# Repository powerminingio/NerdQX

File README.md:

<sup>Revision 1.0</sup>

> The standard and spearhead of current multi-ASIC home miners based on open hardware.

## About

**Powermining fork** changes are - removed USA flag, added Powermining logo

**NerdQX** is a new development based on [NerdQaxe++](https://github.com/shufps/qaxe). NerdQX also has four BM1370 ASIC
chips, a different PCB geometry, and significantly improved and simplified safety mechanisms. 

The NerdQX was developed as the world's first multi-ASIC home miner for overclocking, which also enables extremely 
efficient mining. Furthermore, the NerdQX can measure the temperature of all four ASICs separately and directly, in 
addition to the existing and somewhat less accurate variant. 

NerdQX offers full compatibility with the [ESP Miner NerdQAxe+](https://github.com/shufps/ESP-Miner-NerdQAxePlus) 
firmware, which has been specially enhanced for the NerdQX. This means you get the benefits of ongoing support and 
further development on an open source basis. 

Many small and large improvements make the NerdQX the new standard for multi-ASIC home miners based on open hardware.

## Highlights

### Four ASIC BM1370 processors with clock speeds up to 1000 MHz
> Unique in open-source home mining worldwide – ready for performance or economy mode.

### New PCB design with significantly increased copper and optimized conductor tracks
> The entire layout of the NerdQX has been redesigned electrically and thermally. The use of a significantly higher 
  copper ratio in the conductor tracks significantly improves the current carrying capacity of the board – even 
  under permanently high ASIC loads. The wider spacing and targeted routing ensure stable power supply, reduced heat 
  loss, and more even temperature distribution, while at the same time greatly improving efficiency.

### Dedicated cooling of the VREGs with custom-made heat sinks
> Unlike previous DIY miners, where voltage regulators often remain completely uncooled, NerdQX sets a new standard 
  here: The VREGs have been mechanically offset to enable the best possible airflow and heat dissipation. 
  In combination with a customized, thermally adapted heat sink, the resulting power loss is efficiently dissipated – 
  a concept that has previously only been used in industrial mining rigs. This measure not only extends the service 
  life of the components, but also allows safe overclocking without the risk of thermal instability in the power range 
  for the first time.
  
> **NOTE:** This heatsink is available from [Ix Tech](https://ixtech.xyz) not DigiKey.

### XT60 power connector
> Industry standard: extremely low contact resistance, high current carrying capacity, and reliable contact - even 
  in mobile or vibration-prone setups.

### Mini automotive fuse, set to the NerdQX power rating of 15 amps
> Robust, cost-effective, and easy to replace – provides additional protection against short circuits or overcurrent 
  without the need for complicated safety mechanisms, while allowing for simple visual checks of functionality.

### 4-pin PWM connector for up to three fans or AiO cooling
> Modular, efficient, prepared for quiet or aggressive cooling strategies.

### Rounded PCB corners for better protection and a high-quality overall impression
> A detail that makes safety and manufacturing quality visible.

### Proprietary open-source firmware
> The NerdQX firmware is based on the established open source NerdQaxe++ firmware, but has been specifically 
  enhanced for the new design and architecture of the NerdQX. These adjustments allow the NerdQX to be precisely 
  controlled in the range from underclocking to high-performance operation without compromising security or 
  transparency.

### Significantly improved sensor technology for temperature monitoring of all four ASICs
> Precise temperature measurement allows perfect control over thermal development during cooling. In addition to the 
  not entirely accurate temperature measurement of the ASIC, the NerdQX allows direct measurement and output of the 
  current temperature per ASIC processor for the first time.

## Collaboration

The NerdQX project was developed by an international team of enthusiasts. 

| Ix Tech                                                      | PlebBase                                                         | phil31                                                          | shufps                                                           |
|--------------------------------------------------------------|------------------------------------------------------------------|------------------------------------------------------------------|------------------------------------------------------------------|
|   |  |  |  |
|  |        |                                                                  |                                                                 |
 
> Special thanks go to shufps, who developed the NerdQaxe and the corresponding firmware; without him, much of this would
  not have been possible. Thanks also go to the many other talented developers who have been involved in the Nerd* 
  projects so far.

## Development

The further development of the NerdQX is being actively pursued in order to develop additional ideas and features with
the goal of creating the perfect multi-ASIC home miner that sets new standards.

## Table of Content

* [NerdQX original sources](assets/ORIGINAL_SOURCES.md)
* [NerdQX review on PlebBase](https://plebbase.com/development/all-eyez-nerdqx)
* [Official firmware](https://github.com/shufps/ESP-Miner-NerdQAxePlus)
* [Changelog](assets/CHANGELOG.md) of the project.

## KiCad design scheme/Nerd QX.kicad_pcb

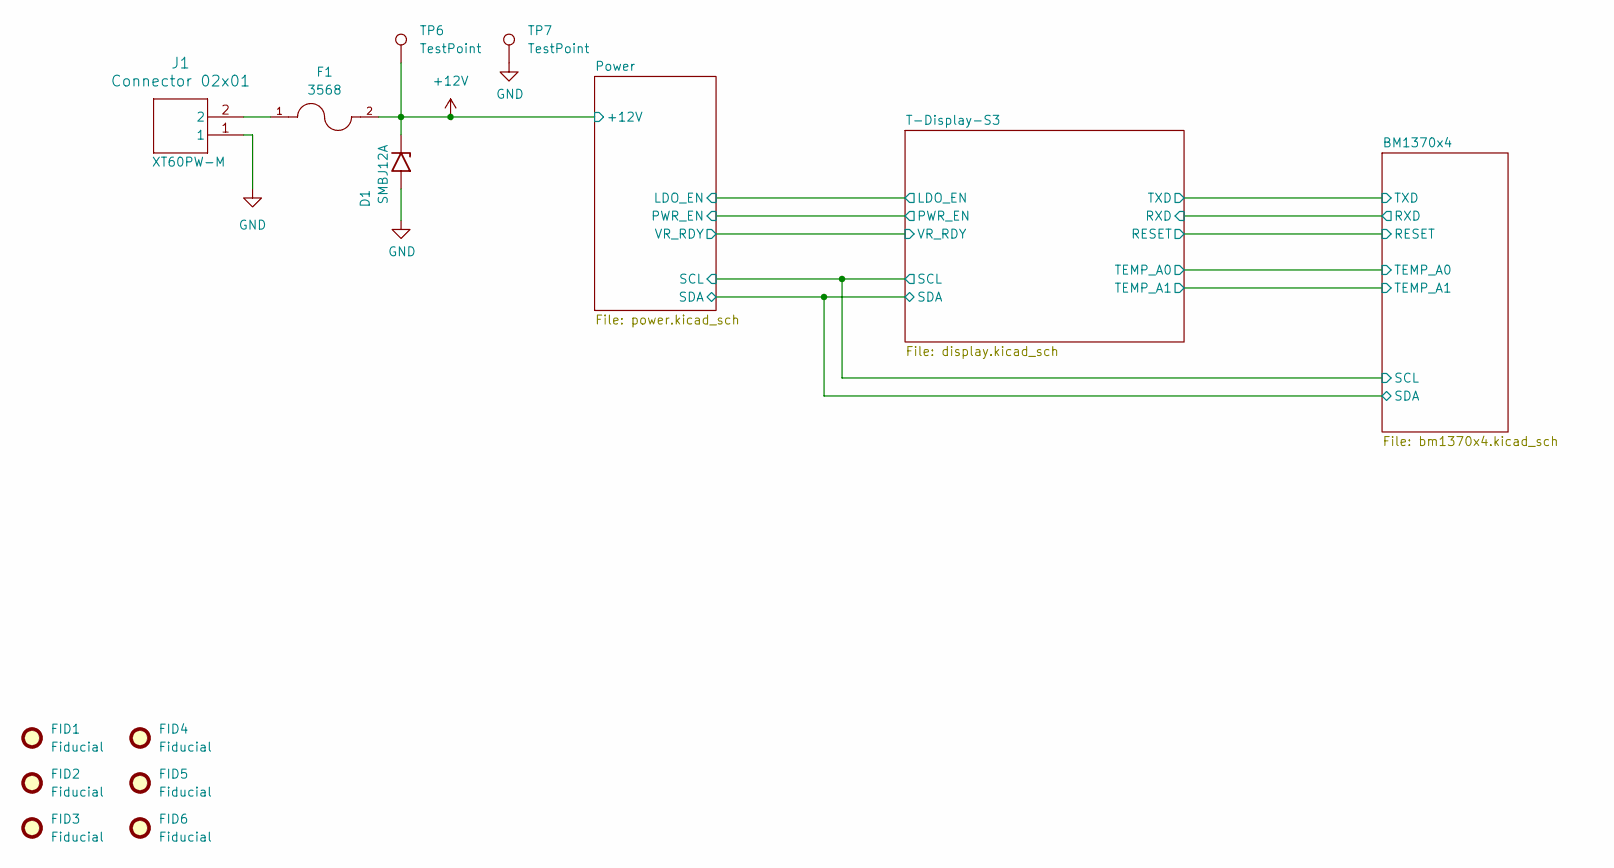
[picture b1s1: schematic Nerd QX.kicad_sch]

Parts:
D1: SMBJ12A; D_SMB
F1: 3568; Fuseholder_Blade_Mini_Keystone_3568
FID1, FID2, FID3, FID4, FID5, FID6: Fiducial; Fiducial_1mm_Mask3mm
J1: Connector 02x01; AMASS_XT60PW-M_1x02_P7.20mm_Horizontal
TP6, TP7: TestPoint; TestPoint_Pad_D2.0mm

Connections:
+12V: D1.1 (A1), F1.2, TP6.1; also elsewhere on the board
GND: D1.2 (A2), J1.1, TP7.1; also elsewhere on the board
unnamed: F1.1, J1.2

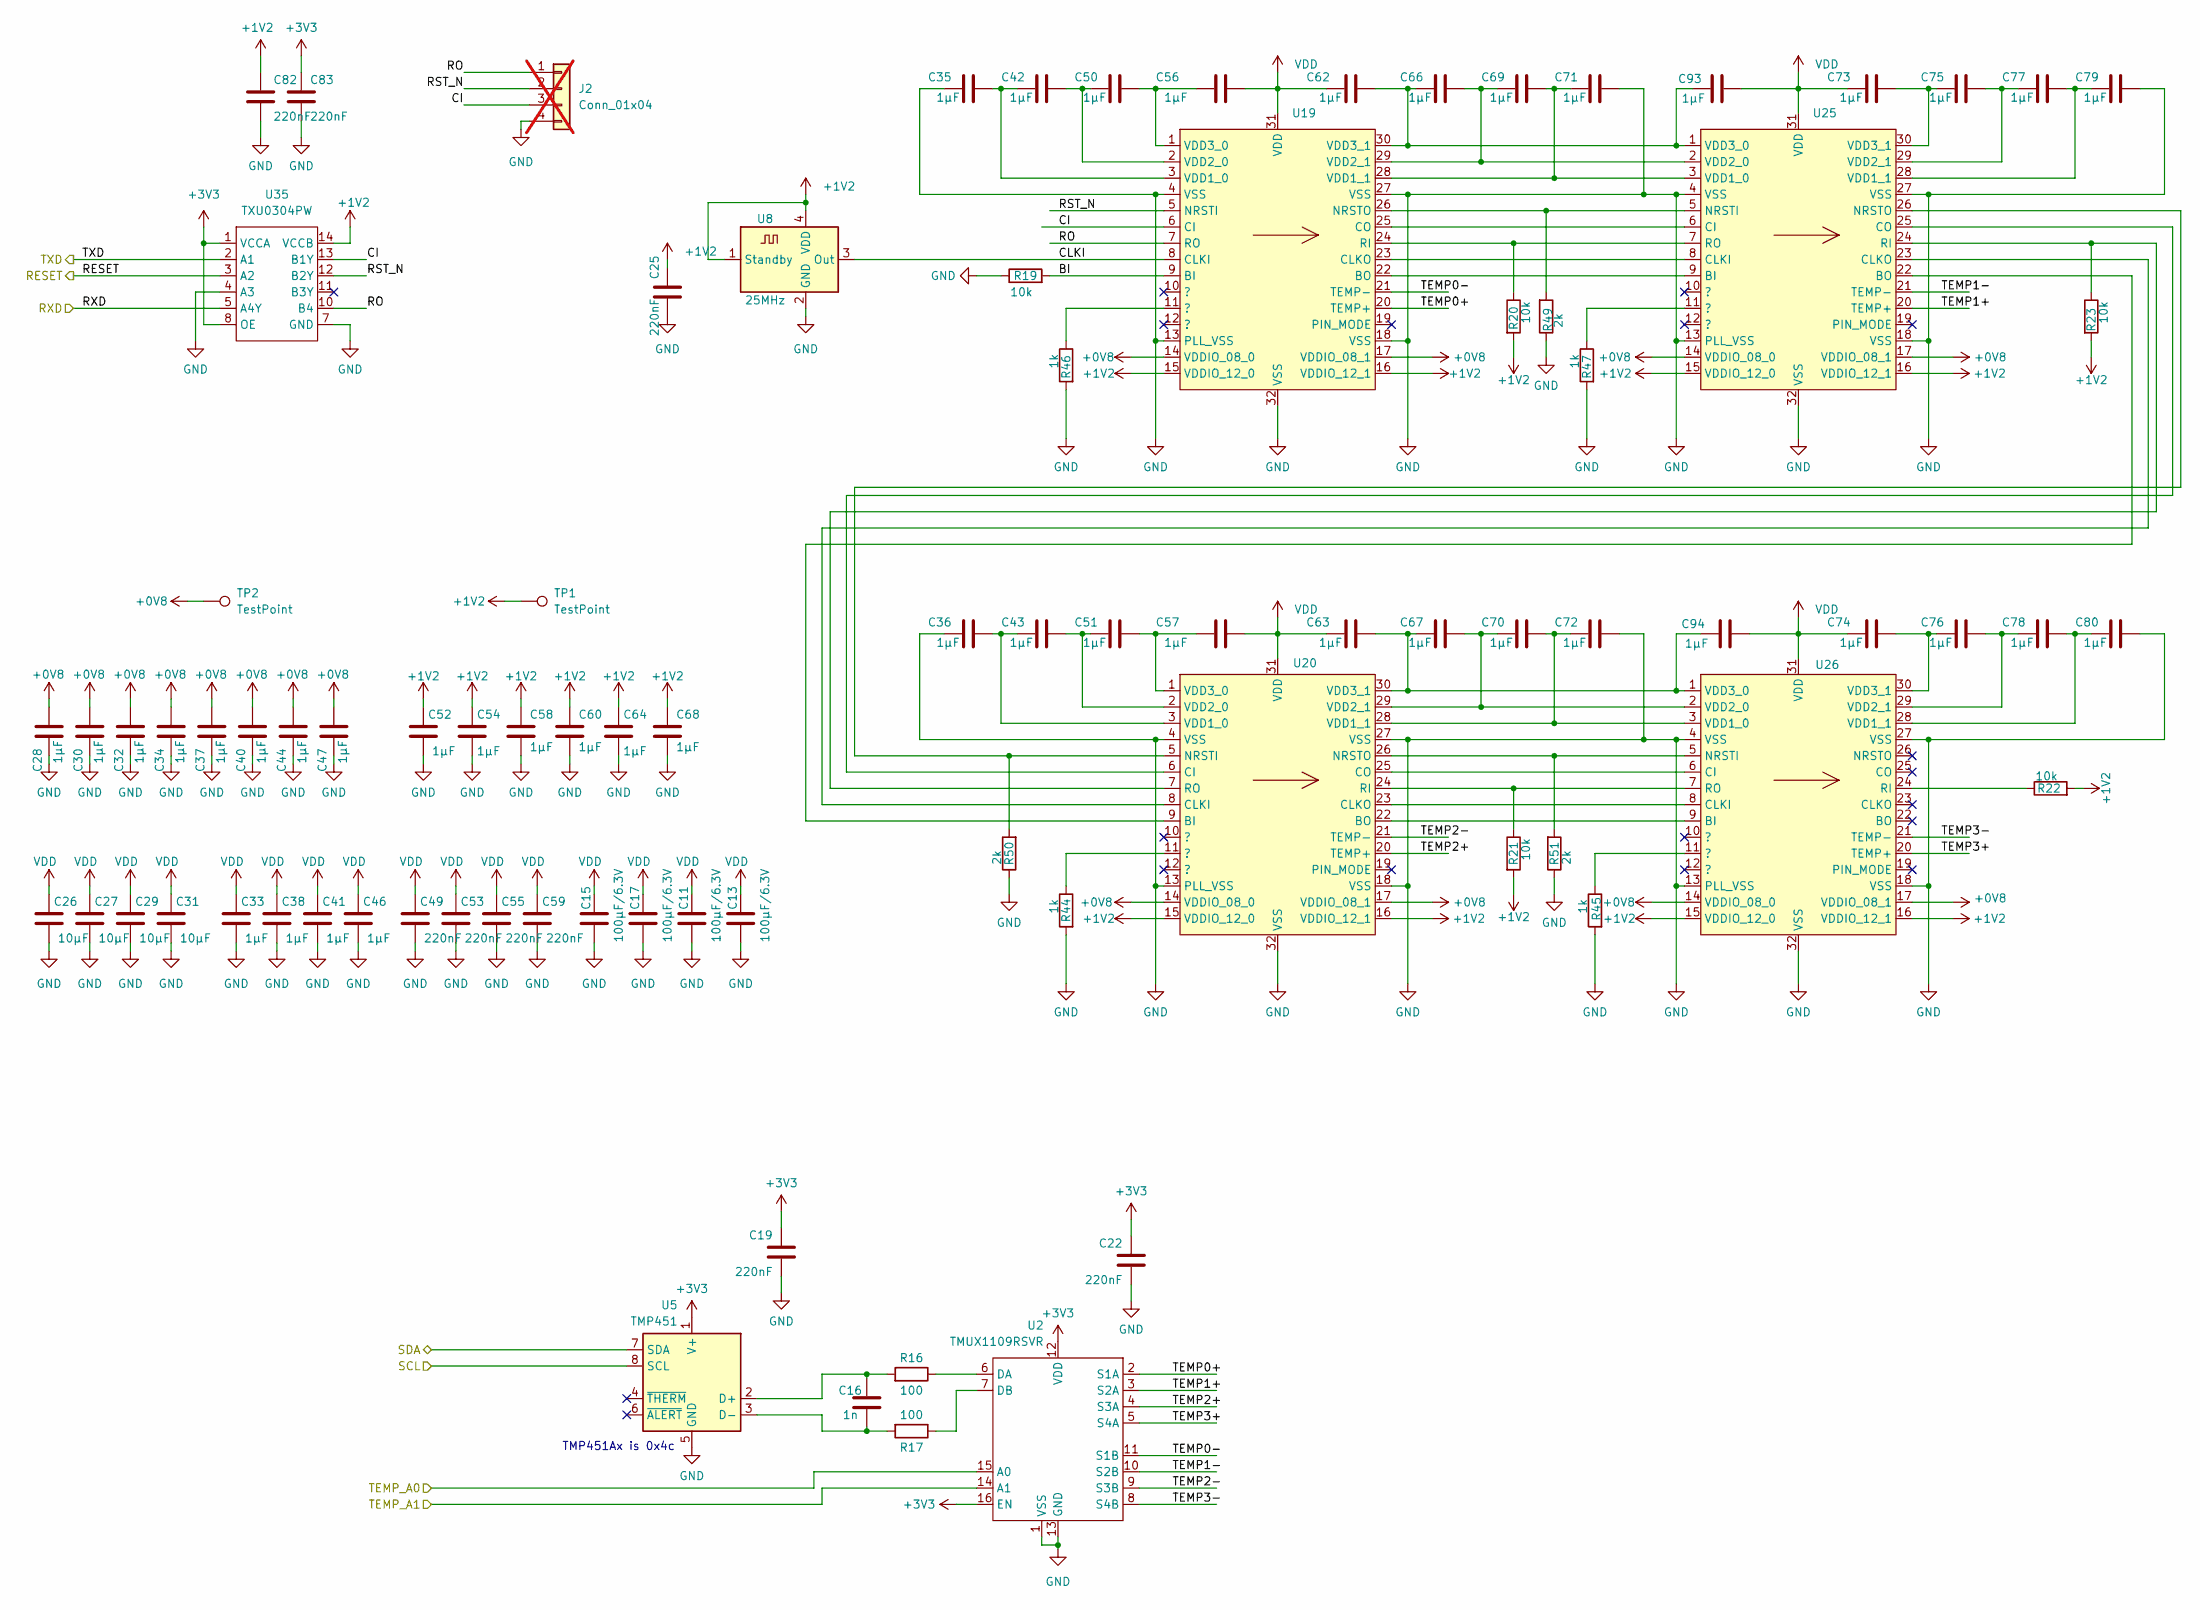
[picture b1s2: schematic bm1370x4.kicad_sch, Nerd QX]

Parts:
C11, C13, C15, C17: 100µF/6.3V; C_1210_3225Metric
C16: 1n; C_0805_2012Metric
C19, C22, C25, C49, C53, C55, C59, C82, C83: 220nF; C_0805_2012Metric
C26, C27, C29, C31: 10µF; C_0805_2012Metric
C28, C30, C32, C33, C34, C35, C36, C37, C38, C40, C41, C42, C43, C44, C46, C47, C50, C51, C52, C54, C56, C57, C58, C60, C62, C63, C64, C66, C67, C68, C69, C70, C71, C72, C73, C74, C75, C76, C77, C78, C79, C80, C93, C94: 1µF; C_0805_2012Metric
J2: Conn_01x04; PinHeader_1x04_P1.27mm_Vertical; not fitted
R16, R17: 100; R_0805_2012Metric
R19, R20, R21, R22, R23: 10k; R_0805_2012Metric
R44, R45, R46, R47: 1k; R_0805_2012Metric
R49, R50, R51: 2k; R_0805_2012Metric
TP1, TP2: TestPoint; TestPoint_Pad_D2.0mm
U2: TMUX1109RSVR; UQFN-16_1.8x2.6mm_P0.4mm
U5: TMP451; WSON-8-1EP_2x2mm_P0.5mm_EP0.9x1.6mm
U8: 25MHz; Oscillator_SMD_EuroQuartz_XO32-4Pin_3.2x2.5mm
U19, U20, U25, U26: BM1370_mode1; BM1370
U35: TXU0304PW; TSSOP-14_4.4x5mm_P0.65mm

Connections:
+0V8: C28.2, C30.2, C32.2, C34.2, C37.2, C40.2, C44.2, C47.2, TP2.1, U19.14 (VDDIO_08_0), U19.17 (VDDIO_08_1), U20.14 (VDDIO_08_0), U20.17 (VDDIO_08_1), U25.14 (VDDIO_08_0), U25.17 (VDDIO_08_1), U26.14 (VDDIO_08_0), U26.17 (VDDIO_08_1); also elsewhere on the board
+1V2: C25.1, C52.1, C54.1, C58.1, C60.1, C64.1, C68.1, C82.1, R20.2, R21.2, R22.2, R23.2, TP1.1, U8.1 (Standby), U8.4 (VDD), U19.15 (VDDIO_12_0), U19.16 (VDDIO_12_1), U20.15 (VDDIO_12_0), U20.16 (VDDIO_12_1), U25.15 (VDDIO_12_0), U25.16 (VDDIO_12_1), U26.15 (VDDIO_12_0), U26.16 (VDDIO_12_1), U35.14 (VCCB); also elsewhere on the board
+3V3: C19.1, C22.1, C83.1, U2.12 (VDD), U2.16 (EN), U5.1 (V+), U35.1 (VCCA), U35.8 (OE); also elsewhere on the board
/BM1370x4/BI: R19.2, U19.9 (BI)
/BM1370x4/CI: J2.3, U19.6 (CI), U35.13 (B1Y)
/BM1370x4/CLKI: U8.3 (Out), U19.8 (CLKI)
/BM1370x4/RESET: U35.3 (A2); also elsewhere on the board
/BM1370x4/RO: J2.1, U19.7 (RO), U35.10 (B4)
/BM1370x4/RST_N: J2.2, U19.5 (NRSTI), U35.12 (B2Y)
/BM1370x4/RXD: U35.5 (A4Y); also elsewhere on the board
/BM1370x4/TEMP0+: U2.2 (S1A), U19.20 (TEMP+)
/BM1370x4/TEMP0-: U2.11 (S1B), U19.21 (TEMP-)
/BM1370x4/TEMP1+: U2.3 (S2A), U25.20 (TEMP+)
/BM1370x4/TEMP1-: U2.10 (S2B), U25.21 (TEMP-)
/BM1370x4/TEMP2+: U2.4 (S3A), U20.20 (TEMP+)
/BM1370x4/TEMP2-: U2.9 (S3B), U20.21 (TEMP-)
/BM1370x4/TEMP3+: U2.5 (S4A), U26.20 (TEMP+)
/BM1370x4/TEMP3-: U2.8 (S4B), U26.21 (TEMP-)
/BM1370x4/TEMP_A0: U2.15 (A0); also elsewhere on the board
/BM1370x4/TEMP_A1: U2.14 (A1); also elsewhere on the board
/BM1370x4/TXD: U35.2 (A1); also elsewhere on the board
/T-Display-S3/SCL: U5.8 (SCL); also elsewhere on the board
/T-Display-S3/SDA: U5.7 (SDA); also elsewhere on the board
GND: C11.2, C13.2, C15.2, C17.2, C19.2, C22.2, C25.2, C26.2, C27.2, C28.1, C29.2, C30.1, C31.2, C32.1, C33.2, C34.1, C35.1, C36.1, C37.1, C38.2, C40.1, C41.2, C44.1, C46.2, C47.1, C49.2, C52.2, C53.2, C54.2, C55.2, C58.2, C59.2, C60.2, C64.2, C68.2, C71.2, C72.2, C79.2, C80.2, C82.2, C83.2, J2.4, R19.1, R44.2, R45.2, R46.2, R47.2, R49.1, R50.1, R51.1, U2.1 (VSS), U2.13 (GND), U5.5 (GND), U8.2 (GND), U19.4 (VSS), U19.13 (PLL_VSS), U19.18 (VSS), U19.27 (VSS), U19.32 (VSS), U20.4 (VSS), U20.13 (PLL_VSS), U20.18 (VSS), U20.27 (VSS), U20.32 (VSS), U25.4 (VSS), U25.13 (PLL_VSS), U25.18 (VSS), U25.27 (VSS), U25.32 (VSS), U26.4 (VSS), U26.13 (PLL_VSS), U26.18 (VSS), U26.27 (VSS), U26.32 (VSS), U35.4 (A3), U35.7 (GND); also elsewhere on the board
unnamed: R44.1, U20.11 (?)
unnamed: R45.1, U26.11 (?)
unnamed: R46.1, U19.11 (?)
unnamed: R47.1, U25.11 (?)
unnamed: R16.1, U2.6 (DA)
unnamed: R17.1, U2.7 (DB)
unnamed: C16.1, R16.2, U5.2 (D+)
unnamed: C16.2, R17.2, U5.3 (D-)
unnamed: U19.22 (BO), U25.9 (BI)
unnamed: U19.23 (CLKO), U25.8 (CLKI)
unnamed: U19.25 (CO), U25.6 (CI)
unnamed: R49.2, U19.26 (NRSTO), U25.5 (NRSTI)
unnamed: R20.1, U19.24 (RI), U25.7 (RO)
unnamed: C35.2, C42.1, U19.3 (VDD1_0)
unnamed: C69.2, C71.1, U19.28 (VDD1_1), U25.3 (VDD1_0)
unnamed: C42.2, C50.1, U19.2 (VDD2_0)
unnamed: C66.2, C69.1, U19.29 (VDD2_1), U25.2 (VDD2_0)
unnamed: C50.2, C56.1, U19.1 (VDD3_0)
unnamed: C62.2, C66.1, C93.1, U19.30 (VDD3_1), U25.1 (VDD3_0)
unnamed: U20.9 (BI), U25.22 (BO)
unnamed: U20.22 (BO), U26.9 (BI)
unnamed: U20.6 (CI), U25.25 (CO)
unnamed: U20.8 (CLKI), U25.23 (CLKO)
unnamed: U20.23 (CLKO), U26.8 (CLKI)
unnamed: U20.25 (CO), U26.6 (CI)
unnamed: R50.2, U20.5 (NRSTI), U25.26 (NRSTO)
unnamed: R51.2, U20.26 (NRSTO), U26.5 (NRSTI)
unnamed: R21.1, U20.24 (RI), U26.7 (RO)
unnamed: R23.1, U20.7 (RO), U25.24 (RI)
unnamed: C36.2, C43.1, U20.3 (VDD1_0)
unnamed: C70.2, C72.1, U20.28 (VDD1_1), U26.3 (VDD1_0)
unnamed: C43.2, C51.1, U20.2 (VDD2_0)
unnamed: C67.2, C70.1, U20.29 (VDD2_1), U26.2 (VDD2_0)
unnamed: C51.2, C57.1, U20.1 (VDD3_0)
unnamed: C63.2, C67.1, C94.1, U20.30 (VDD3_1), U26.1 (VDD3_0)
unnamed: C77.2, C79.1, U25.28 (VDD1_1)
unnamed: C75.2, C77.1, U25.29 (VDD2_1)
unnamed: C73.2, C75.1, U25.30 (VDD3_1)
unnamed: R22.1, U26.24 (RI)
unnamed: C78.2, C80.1, U26.28 (VDD1_1)
unnamed: C76.2, C78.1, U26.29 (VDD2_1)
unnamed: C74.2, C76.1, U26.30 (VDD3_1)
VDD: C11.1, C13.1, C15.1, C17.1, C26.1, C27.1, C29.1, C31.1, C33.1, C38.1, C41.1, C46.1, C49.1, C53.1, C55.1, C56.2, C57.2, C59.1, C62.1, C63.1, C73.1, C74.1, C93.2, C94.2, U19.31 (VDD), U20.31 (VDD), U25.31 (VDD), U26.31 (VDD); also elsewhere on the board

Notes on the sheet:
TMP451Ax is 0x4c

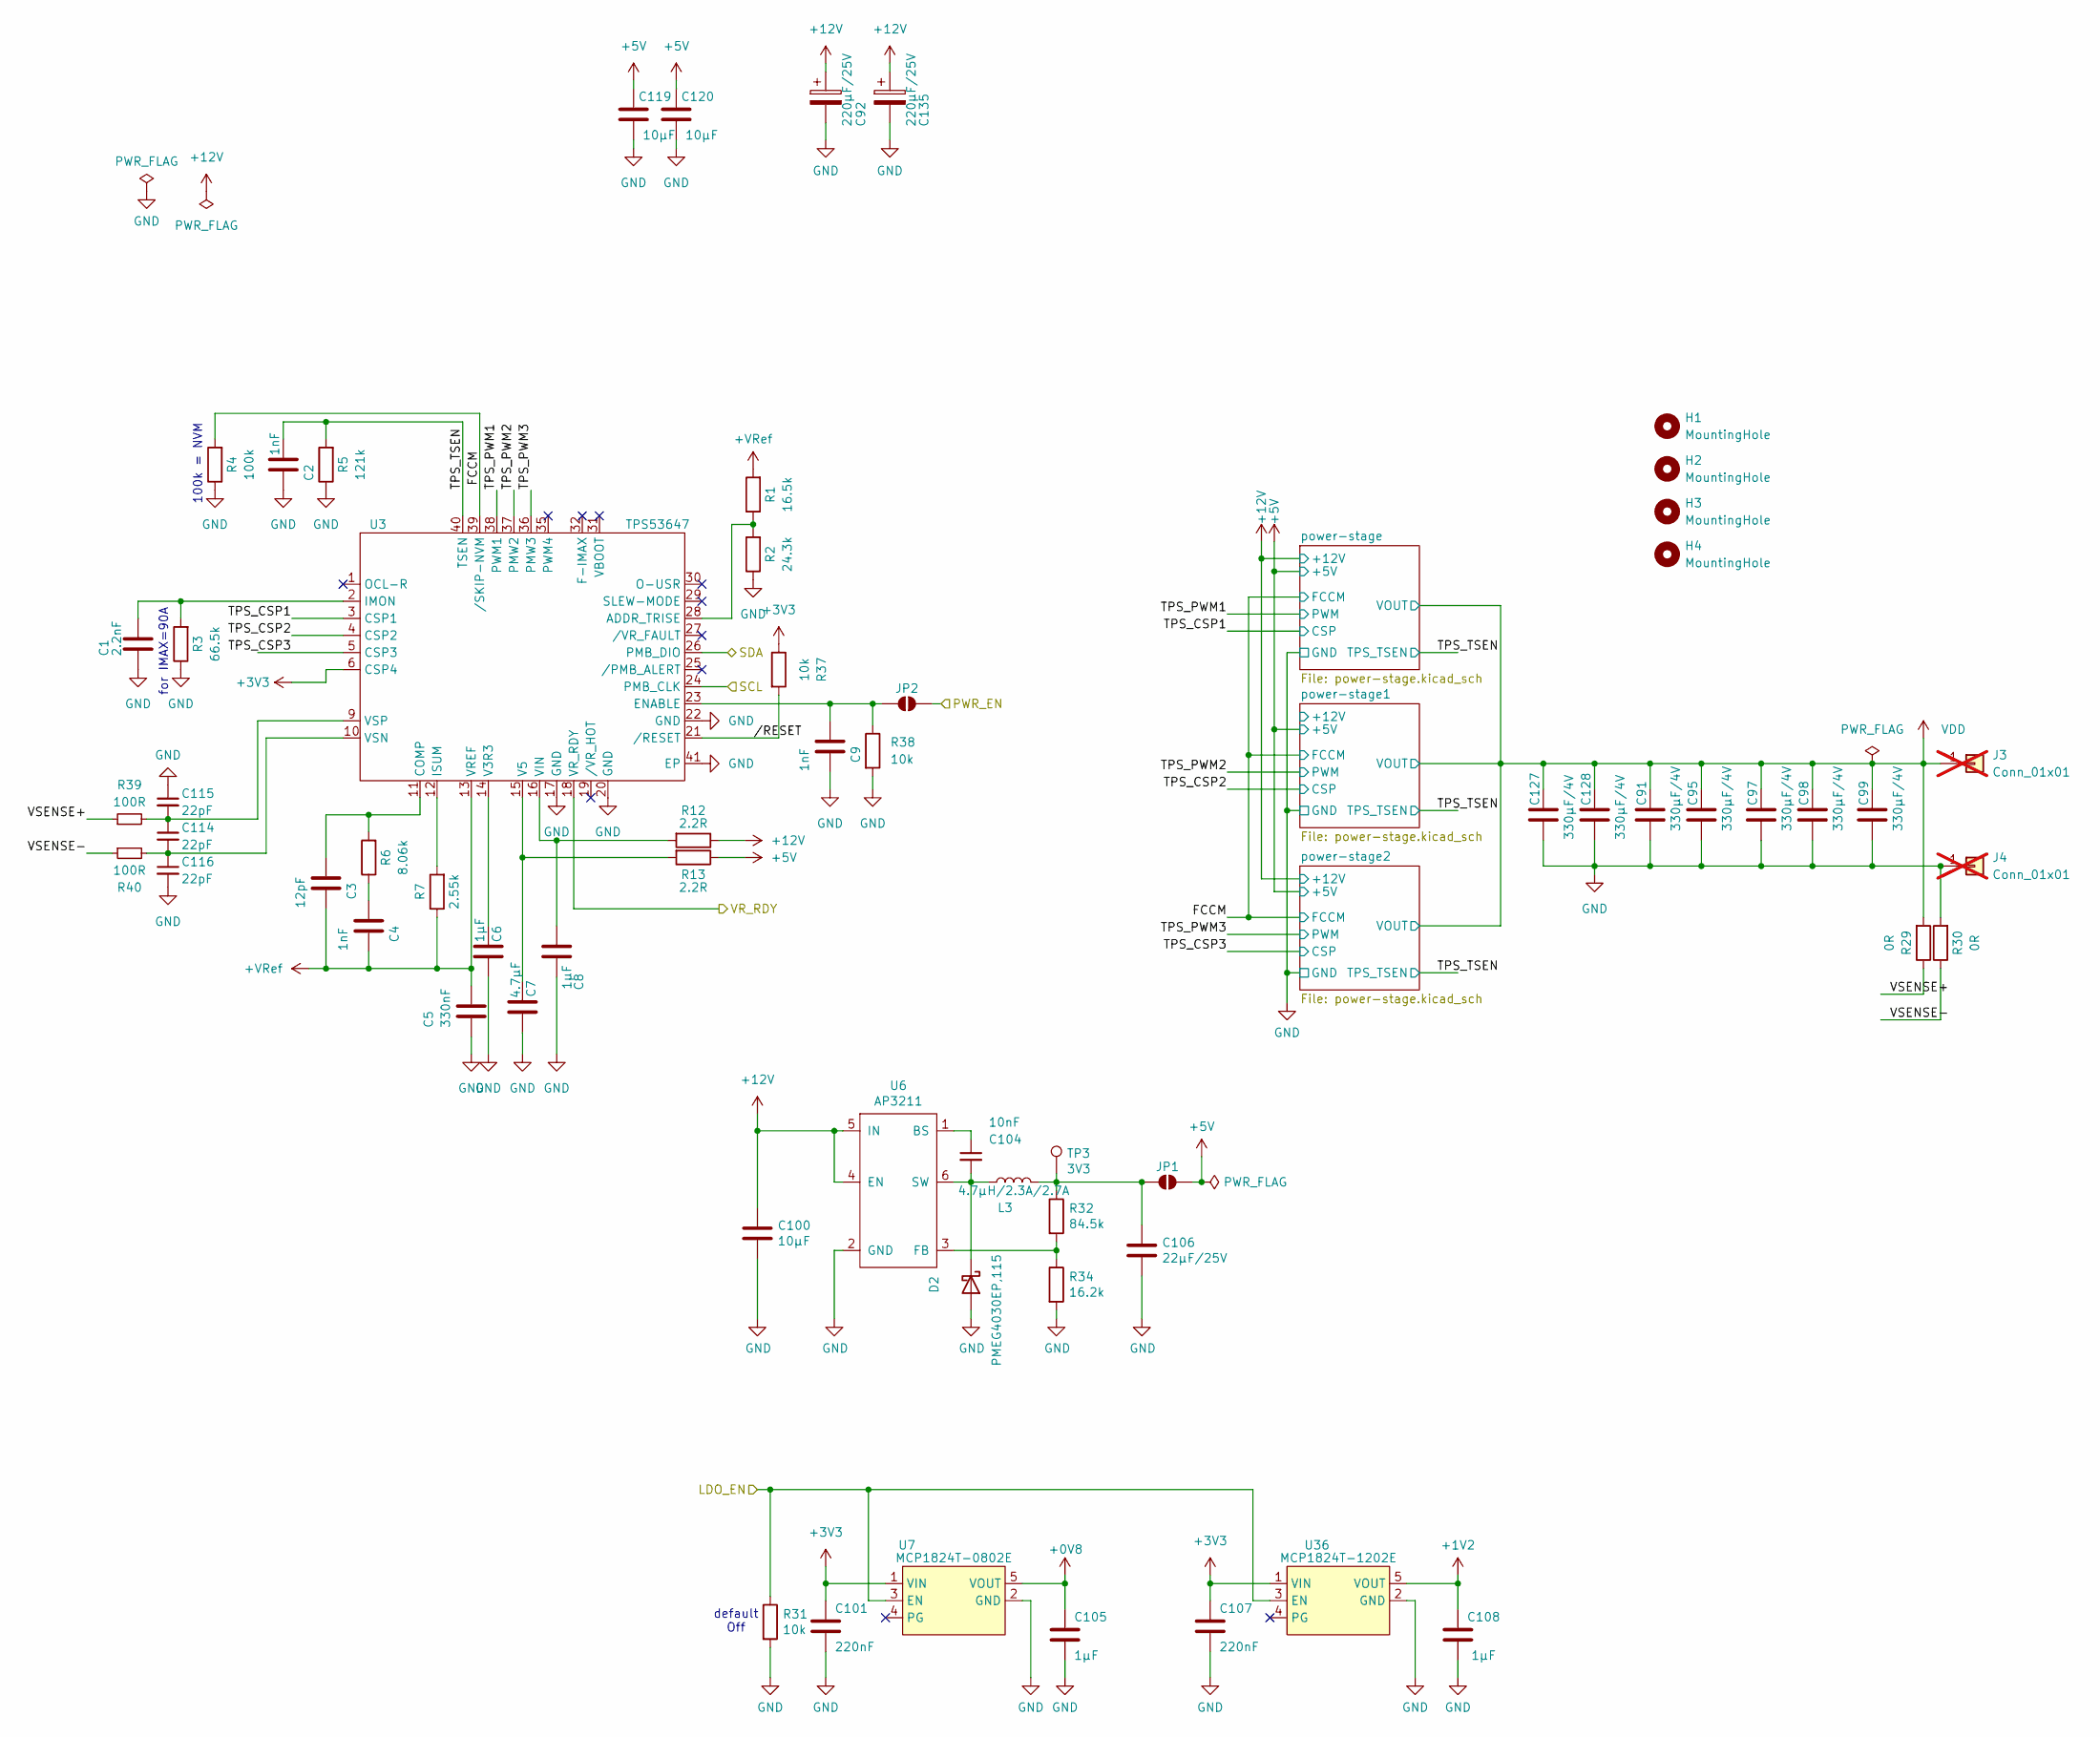
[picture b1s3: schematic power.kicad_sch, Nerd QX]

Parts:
C1: 2.2nF; C_0805_2012Metric
C2, C4, C9: 1nF; C_0805_2012Metric
C3: 12pF; C_0603_1608Metric
C5: 330nF; C_0805_2012Metric
C6, C8, C105, C108: 1µF; C_0805_2012Metric
C7: 4.7µF; C_0805_2012Metric
C91, C95, C97, C98, C99, C127, C128: 330µF/4V; C_1210_3225Metric
C92, C135: 220µF/25V; CP_Elec_8x10
C100, C119, C120: 10µF; C_0805_2012Metric
C101, C107: 220nF; C_0805_2012Metric
C104: 10nF; C_0805_2012Metric
C106: 22µF/25V; C_1210_3225Metric
C114, C115, C116: 22pF; C_0603_1608Metric
D2: PMEG4030EP,115; D_SOD-128
H1, H2, H3, H4: MountingHole; MountingHole_3.2mm_M3_DIN965_Pad_TopBottom
J3, J4: Conn_01x01; Wuerth_REDCUBE-THR_WP-THRBU_74650194_THR; not fitted
JP1, JP2: SolderJumper_2_Open; SolderJumper-2_P1.3mm_Open_RoundedPad1.0x1.5mm
L3: 4.7µH/2.3A/2.7A; L_Taiyo-Yuden_NR-50xx
R1: 16.5k; R_0805_2012Metric
R2: 24.3k; R_0805_2012Metric
R3: 66.5k; R_0805_2012Metric
R4: 100k; R_0805_2012Metric
R5: 121k; R_0805_2012Metric
R6: 8.06k; R_0805_2012Metric
R7: 2.55k; R_0805_2012Metric
R12, R13: 2.2R; R_0805_2012Metric
R29, R30: 0R; R_0805_2012Metric
R31, R37, R38: 10k; R_0805_2012Metric
R32: 84.5k; R_0805_2012Metric
R34: 16.2k; R_0805_2012Metric
R39, R40: 100R; R_0805_2012Metric
TP3: 3V3; TestPoint_Pad_2.0x2.0mm
U3: TPS53647; Texas_RHA0040B_VQFN-40-1EP_6x6mm_P0.5mm_EP4.15x4.15mm_Therm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
U6: AP3211; SOT-23-6
U7: MCP1824T-0802E; SOT-23-5
U36: MCP1824T-1202E; SOT-23-5

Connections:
+0V8: C105.1, U7.5 (VOUT); also elsewhere on the board
+1V2: C108.1, U36.5 (VOUT); also elsewhere on the board
+3V3: C101.1, C107.1, R37.1, U3.6 (CSP4), U7.1 (VIN), U36.1 (VIN); also elsewhere on the board
+5V: C119.1, C120.1, JP1.2 (B), R13.1; also elsewhere on the board
+12V: C92.1, C100.1, C135.1, R12.1, U6.4 (EN), U6.5 (IN); also elsewhere on the board
+VRef: C3.2, C4.2, C5.1, R1.2, R7.1, U3.13 (VREF); also elsewhere on the board
/Power/FCCM: R4.2, U3.39 (/SKIP-NVM); also elsewhere on the board
/Power/LDO_EN: R31.1, U7.3 (EN), U36.3 (EN); also elsewhere on the board
/Power/PWR_EN: JP2.2 (B); also elsewhere on the board
/Power/TPS_CSP1: U3.3 (CSP1); also elsewhere on the board
/Power/TPS_CSP2: U3.4 (CSP2); also elsewhere on the board
/Power/TPS_CSP3: U3.5 (CSP3); also elsewhere on the board
/Power/TPS_PWM1: U3.38 (PWM1); also elsewhere on the board
/Power/TPS_PWM2: U3.37 (PMW2); also elsewhere on the board
/Power/TPS_PWM3: U3.36 (PMW3); also elsewhere on the board
/Power/TPS_TSEN: C2.1, R5.2, U3.40 (TSEN); also elsewhere on the board
/Power/VR_RDY: U3.18 (VR_RDY); also elsewhere on the board
/Power/VSENSE+: R29.1, R39.1
/Power/VSENSE-: R30.1, R40.1
/Power//RESET: R37.2, U3.21 (/RESET)
/T-Display-S3/SCL: U3.24 (PMB_CLK); also elsewhere on the board
/T-Display-S3/SDA: U3.26 (PMB_DIO); also elsewhere on the board
GND: C1.2, C2.2, C5.2, C6.2, C7.1, C8.1, C9.2, C91.2, C92.2, C95.2, C97.2, C98.2, C99.2, C100.2, C101.2, C105.2, C106.2, C107.2, C108.2, C115.1, C116.2, C119.2, C120.2, C127.2, C128.2, C135.2, D2.2 (A), J4.1, R2.1, R3.1, R4.1, R5.1, R30.2, R31.2, R34.2, R38.2, U3.17 (GND), U3.20 (GND), U3.22 (GND), U3.41 (EP), U6.2 (GND), U7.2 (GND), U36.2 (GND); also elsewhere on the board
unnamed: C4.1, R6.1
unnamed: C104.2, D2.1 (K), L3.1, U6.6 (SW)
unnamed: C106.1, JP1.1 (A), L3.2, R32.1, TP3.1
unnamed: C9.1, JP2.1 (A), R38.1, U3.23 (ENABLE)
unnamed: R1.1, R2.2, U3.28 (ADDR_TRISE)
unnamed: C3.1, R6.2, U3.11 (COMP)
unnamed: C1.1, R3.2, U3.2 (IMON)
unnamed: R7.2, U3.12 (ISUM)
unnamed: C6.1, U3.14 (V3R3)
unnamed: C7.2, R13.2, U3.15 (V5)
unnamed: C8.2, R12.2, U3.16 (VIN)
unnamed: C114.2, C116.1, R40.2, U3.10 (VSN)
unnamed: C114.1, C115.2, R39.2, U3.9 (VSP)
unnamed: C104.1, U6.1 (BS)
unnamed: R32.2, R34.1, U6.3 (FB)
VDD: C91.1, C95.1, C97.1, C98.1, C99.1, C127.1, C128.1, J3.1, R29.2; also elsewhere on the board

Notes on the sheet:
default Off
for IMAX=90A
100k = NVM

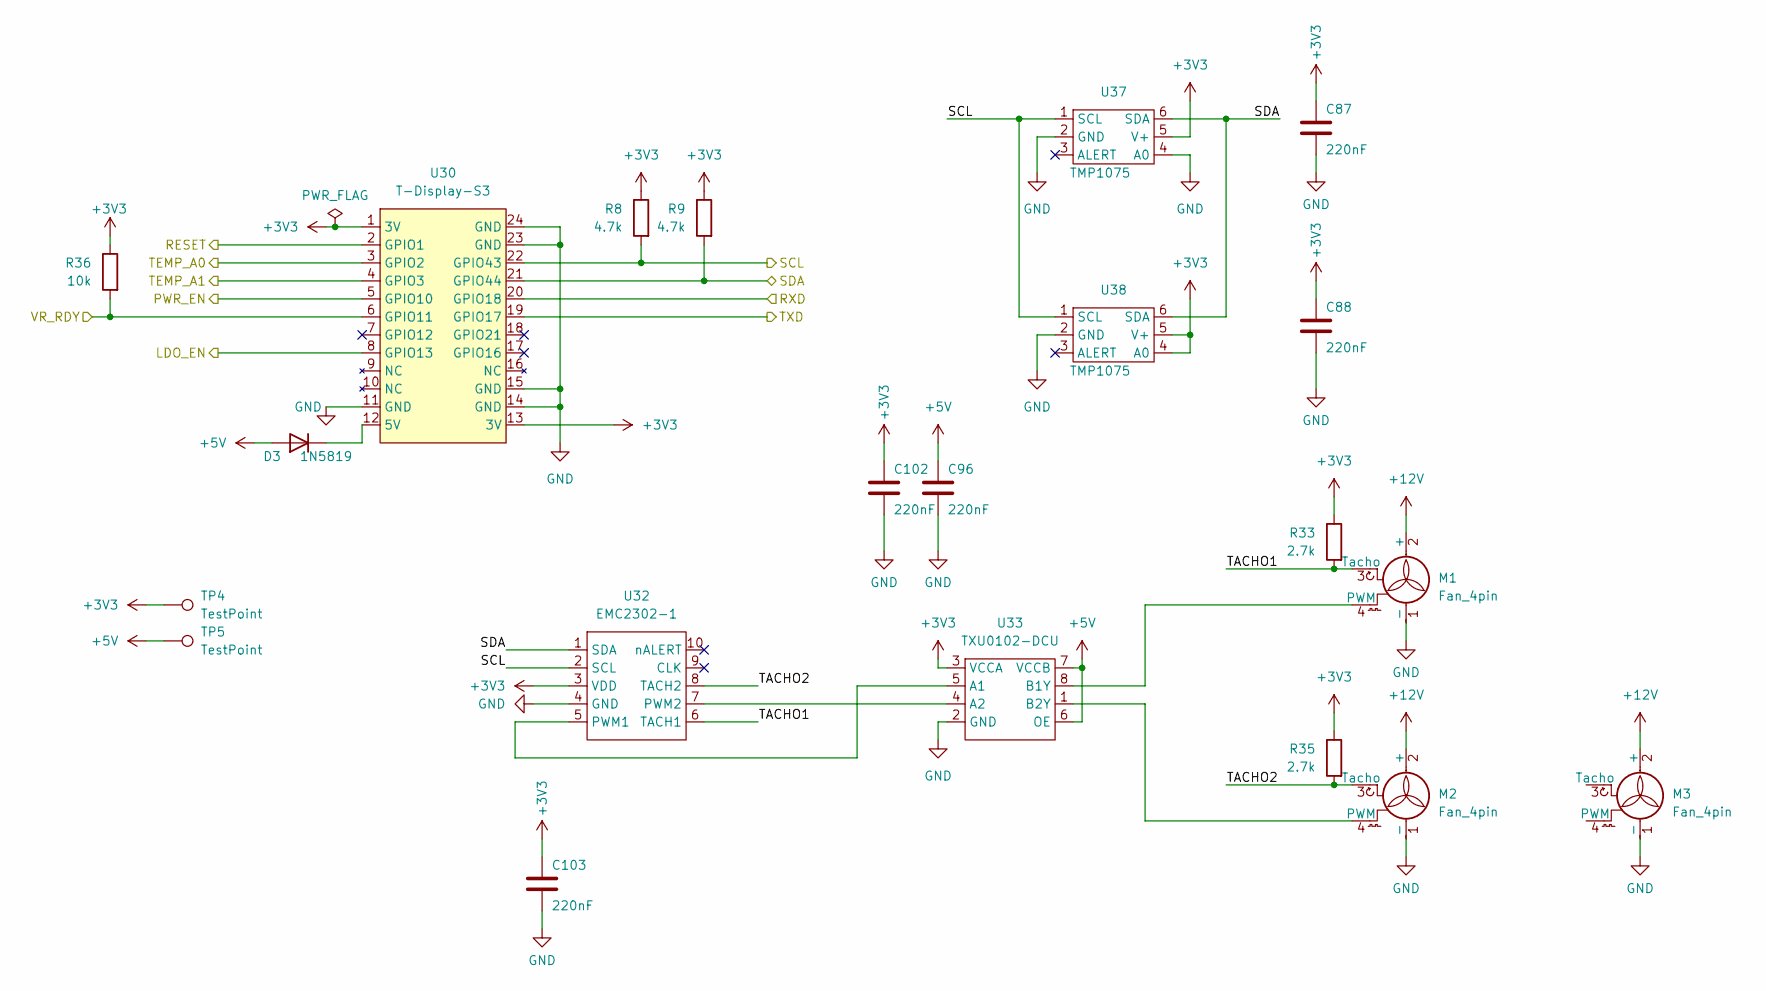
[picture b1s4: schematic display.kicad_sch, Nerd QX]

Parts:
C87, C88, C96, C102, C103: 220nF; C_0805_2012Metric
D3: 1N5819; D_SOD-123
M1, M2, M3: Fan_4pin; FanPinHeader_1x04_P2.54mm_Vertical
R8, R9: 4.7k; R_0805_2012Metric
R33, R35: 2.7k; R_0805_2012Metric
R36: 10k; R_0805_2012Metric
TP4, TP5: TestPoint; TestPoint_Pad_D2.0mm
U30: T-Display-S3
U32: EMC2302-1; MSOP-10_3x3mm_P0.5mm
U33: TXU0102-DCU; VSSOP-8_2.3x2mm_P0.5mm
U37, U38: TMP1075; SOT-563

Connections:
+3V3: C87.1, C88.1, C102.1, C103.1, R8.1, R9.1, R33.1, R35.1, R36.1, TP4.1, U30.1 (3V), U30.13 (3V), U32.3 (VDD), U33.3 (VCCA), U37.5 (V+), U38.4 (A0), U38.5 (V+); also elsewhere on the board
+5V: C96.1, D3.2 (A), TP5.1, U33.6 (OE), U33.7 (VCCB); also elsewhere on the board
+12V: M1.2 (+), M2.2 (+), M3.2 (+); also elsewhere on the board
/BM1370x4/RESET: U30.2 (GPIO1); also elsewhere on the board
/BM1370x4/RXD: U30.20 (GPIO18); also elsewhere on the board
/BM1370x4/TEMP_A0: U30.3 (GPIO2); also elsewhere on the board
/BM1370x4/TEMP_A1: U30.4 (GPIO3); also elsewhere on the board
/BM1370x4/TXD: U30.19 (GPIO17); also elsewhere on the board
/Power/LDO_EN: U30.8 (GPIO13); also elsewhere on the board
/Power/PWR_EN: U30.5 (GPIO10); also elsewhere on the board
/Power/VR_RDY: R36.2, U30.6 (GPIO11); also elsewhere on the board
/T-Display-S3/SCL: R8.2, U30.22 (GPIO43), U32.2 (SCL), U37.1 (SCL), U38.1 (SCL); also elsewhere on the board
/T-Display-S3/SDA: R9.2, U30.21 (GPIO44), U32.1 (SDA), U37.6 (SDA), U38.6 (SDA); also elsewhere on the board
/T-Display-S3/TACHO1: M1.3 (Tacho), R33.2, U32.6 (TACH1)
/T-Display-S3/TACHO2: M2.3 (Tacho), R35.2, U32.8 (TACH2)
GND: C87.2, C88.2, C96.2, C102.2, C103.2, M1.1 (-), M2.1 (-), M3.1 (-), U30.11 (GND), U30.14 (GND), U30.15 (GND), U30.23 (GND), U30.24 (GND), U32.4 (GND), U33.2 (GND), U37.2 (GND), U37.4 (A0), U38.2 (GND); also elsewhere on the board
unnamed: D3.1 (K), U30.12 (5V)
unnamed: M1.4 (PWM), U33.8 (B1Y)
unnamed: M2.4 (PWM), U33.1 (B2Y)
unnamed: U32.5 (PWM1), U33.5 (A1)
unnamed: U32.7 (PWM2), U33.4 (A2)

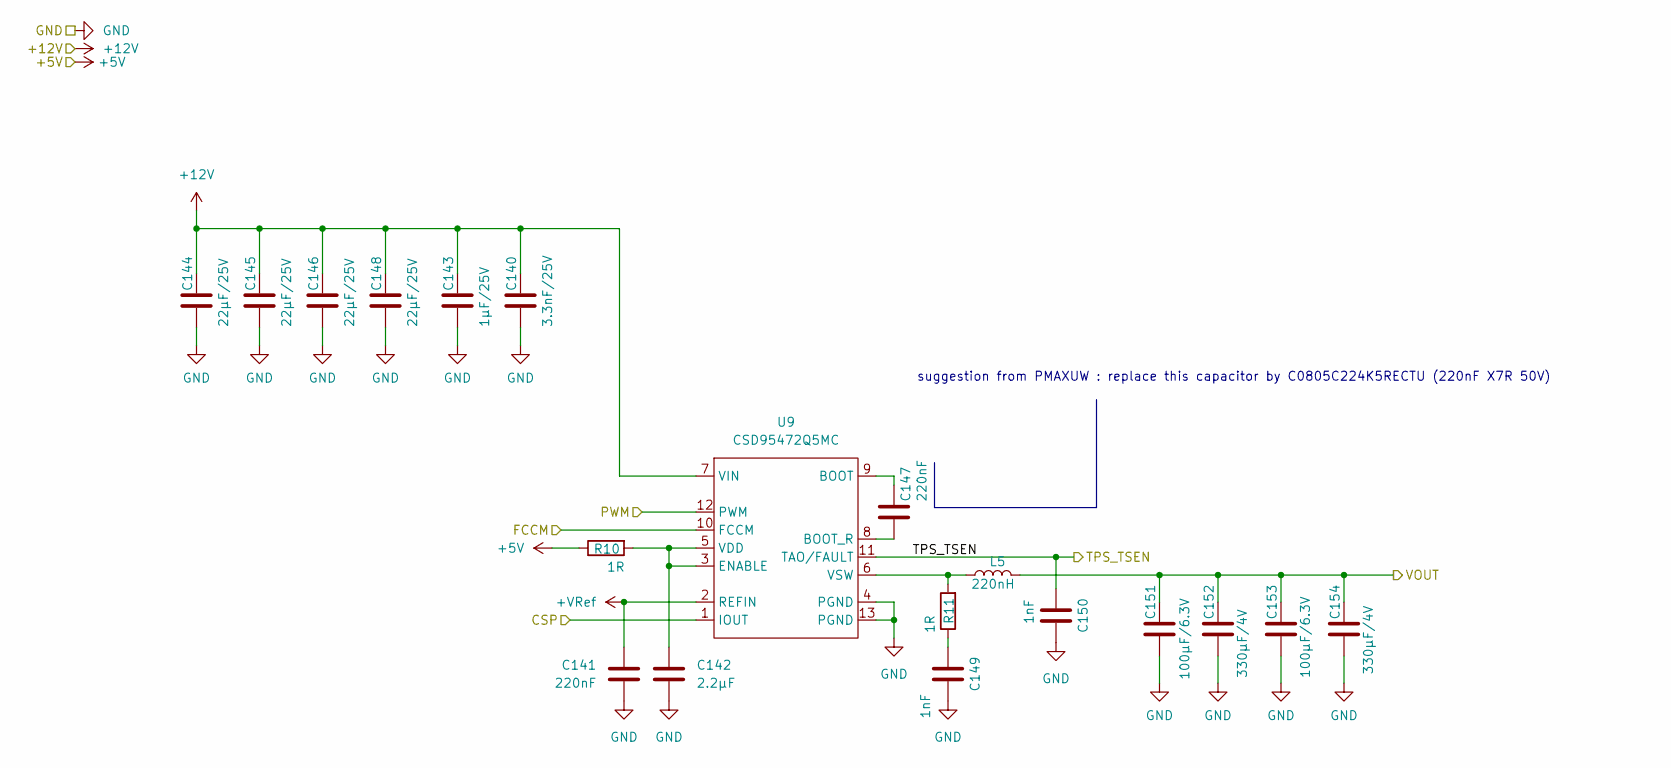
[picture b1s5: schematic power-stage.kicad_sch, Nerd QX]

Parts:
C140: 3.3nF/25V; C_0805_2012Metric
C141, C147: 220nF; C_0805_2012Metric
C142: 2.2µF; C_0805_2012Metric
C143: 1µF/25V; C_0805_2012Metric
C144, C145, C146, C148: 22µF/25V; C_1210_3225Metric
C149, C150: 1nF; C_0805_2012Metric
C151, C153: 100µF/6.3V; C_1210_3225Metric
C152, C154: 330µF/4V; C_1210_3225Metric
L5: 220nH; IFLR-4031GC-01-8x10
R10, R11: 1R; R_0805_2012Metric
U9: CSD95472Q5MC

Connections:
+5V: R10.1; also elsewhere on the board
+12V: C140.1, C143.1, C144.1, C145.1, C146.1, C148.1, U9.7 (VIN); also elsewhere on the board
+VRef: C141.1, U9.2 (REFIN); also elsewhere on the board
/Power/FCCM: U9.10 (FCCM); also elsewhere on the board
/Power/TPS_CSP2: U9.1 (IOUT); also elsewhere on the board
/Power/TPS_PWM2: U9.12 (PWM); also elsewhere on the board
/Power/TPS_TSEN: C150.1, U9.11 (TAO/FAULT); also elsewhere on the board
GND: C140.2, C141.2, C142.2, C143.2, C144.2, C145.2, C146.2, C148.2, C149.2, C150.2, C151.2, C152.2, C153.2, C154.2, U9.4 (PGND), U9.13 (PGND); also elsewhere on the board
unnamed: C149.1, R11.1
unnamed: C147.1, U9.9 (BOOT)
unnamed: C147.2, U9.8 (BOOT_R)
unnamed: C142.1, R10.2, U9.3 (ENABLE), U9.5 (VDD)
unnamed: L5.1, R11.2, U9.6 (VSW)
VDD: C151.1, C152.1, C153.1, C154.1, L5.2; also elsewhere on the board

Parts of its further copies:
C10, C14, C156, C162: 220nF; C_0805_2012Metric
C12, C157: 2.2µF; C_0805_2012Metric
C18, C109, C164, C165: 1nF; C_0805_2012Metric
C20, C23, C81, C89, C159, C160, C161, C163: 22µF/25V; C_1210_3225Metric
C21, C24, C166, C168: 100µF/6.3V; C_1210_3225Metric
C86, C90, C167, C169: 330µF/4V; C_1210_3225Metric
C117, C155: 3.3nF/25V; C_0805_2012Metric
C118, C158: 1µF/25V; C_0805_2012Metric
L1, L6: 220nH; IFLR-4031GC-01-8x10
R14, R15, R25, R27: 1R; R_0805_2012Metric
U4, U10: CSD95472Q5MC

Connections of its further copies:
+5V: R14.1, R25.1; also elsewhere on the board
+12V: C20.1, C23.1, C81.1, C89.1, C117.1, C118.1, C155.1, C158.1, C159.1, C160.1, C161.1, C163.1, U4.7 (VIN), U10.7 (VIN); also elsewhere on the board
+VRef: C10.1, C156.1, U4.2 (REFIN), U10.2 (REFIN); also elsewhere on the board
/Power/FCCM: U4.10 (FCCM), U10.10 (FCCM); also elsewhere on the board
/Power/TPS_CSP1: U4.1 (IOUT); also elsewhere on the board
/Power/TPS_CSP3: U10.1 (IOUT); also elsewhere on the board
/Power/TPS_PWM1: U4.12 (PWM); also elsewhere on the board
/Power/TPS_PWM3: U10.12 (PWM); also elsewhere on the board
/Power/TPS_TSEN: C109.1, C165.1, U4.11 (TAO/FAULT), U10.11 (TAO/FAULT); also elsewhere on the board
GND: C10.2, C12.2, C18.2, C20.2, C21.2, C23.2, C24.2, C81.2, C86.2, C89.2, C90.2, C109.2, C117.2, C118.2, C155.2, C156.2, C157.2, C158.2, C159.2, C160.2, C161.2, C163.2, C164.2, C165.2, C166.2, C167.2, C168.2, C169.2, U4.4 (PGND), U4.13 (PGND), U10.4 (PGND), U10.13 (PGND); also elsewhere on the board
unnamed: C18.1, R27.1
unnamed: C164.1, R15.1
unnamed: C14.1, U4.9 (BOOT)
unnamed: C14.2, U4.8 (BOOT_R)
unnamed: C12.1, R25.2, U4.3 (ENABLE), U4.5 (VDD)
unnamed: L1.1, R27.2, U4.6 (VSW)
unnamed: C162.1, U10.9 (BOOT)
unnamed: C162.2, U10.8 (BOOT_R)
unnamed: C157.1, R14.2, U10.3 (ENABLE), U10.5 (VDD)
unnamed: L6.1, R15.2, U10.6 (VSW)
VDD: C21.1, C24.1, C86.1, C90.1, C166.1, C167.1, C168.1, C169.1, L1.2, L6.2; also elsewhere on the board

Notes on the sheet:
suggestion from PMAXUW : replace this capacitor by C0805C224K5RECTU (220nF X7R 50V)
